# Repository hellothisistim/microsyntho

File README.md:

# microsyntho
Making synthesizers with microcontrollers

So, yeah... I'm learning about it. And it'll all get dumped here.

License: [CC-BY-SA](https://creativecommons.org/licenses/by-sa/4.0/)

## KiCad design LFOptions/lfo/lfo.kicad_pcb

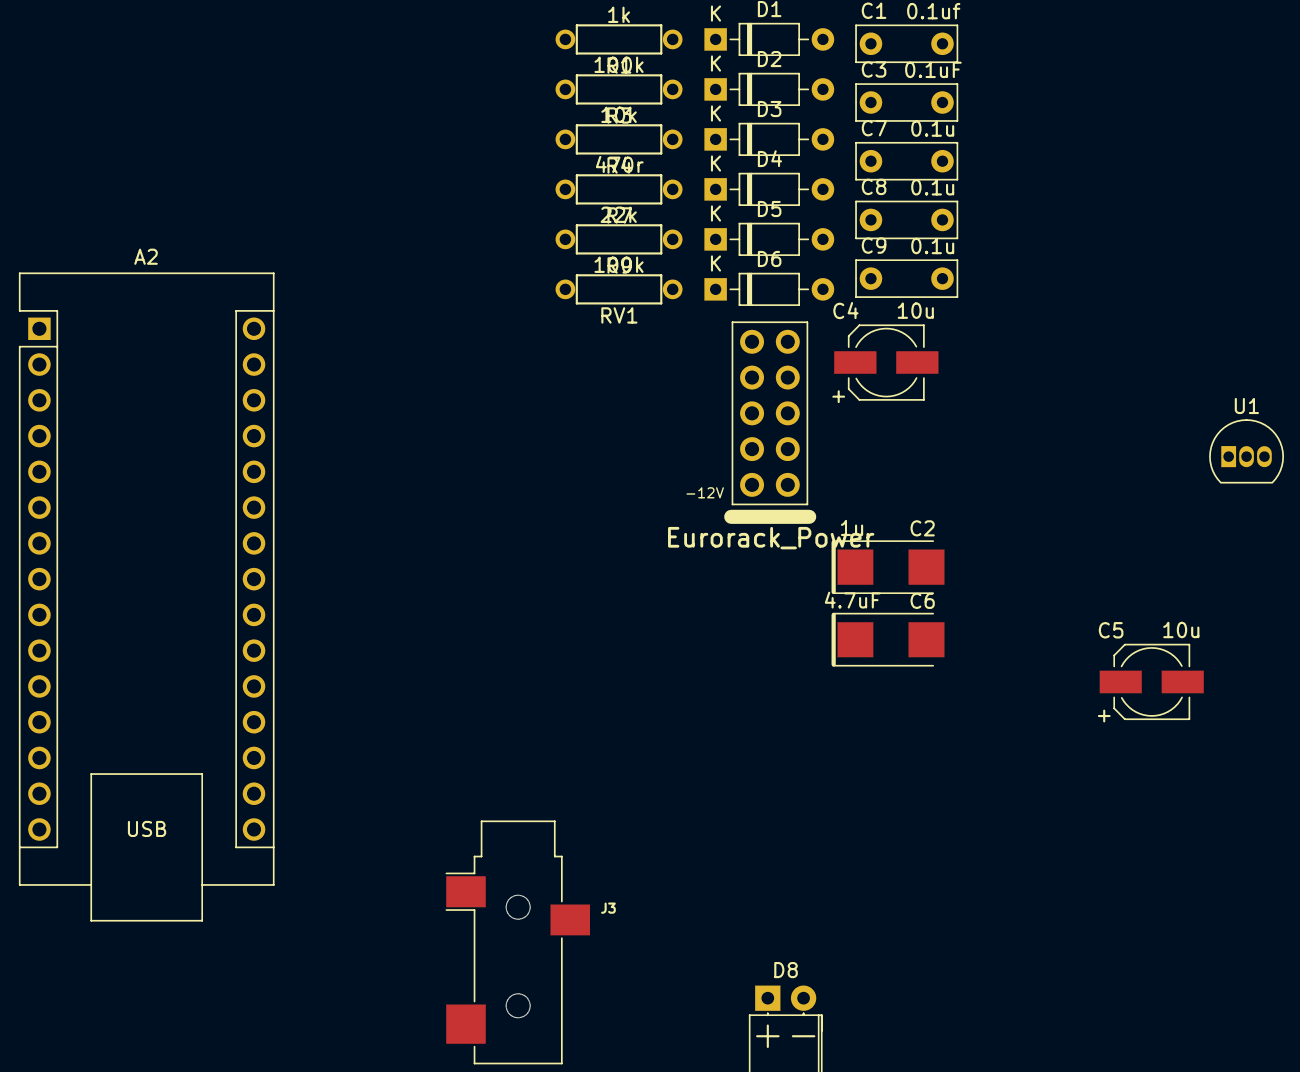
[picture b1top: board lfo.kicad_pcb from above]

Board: 2 copper layers, 26 parts (0 on the bottom side), 14 nets, no tracks yet.

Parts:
A2: Arduino_Nano_v3.x; Arduino_Nano
C1: 0.1uf; C_Disc_P5.08mm
C2: 1u; CP_Tantalum_EIA-6032-28_Kemet-C
C3: 0.1uF; C_Disc_P5.08mm
C4, C5: 10u; CP_Elec_5x5.3
C6: 4.7uF; CP_Tantalum_EIA-6032-28_Kemet-C
C7, C8, C9: 0.1u; C_Disc_P5.08mm
D1, D2, D3, D4, D5, D6: BAT43; D_DO-35_SOD27_P7.62mm_Horizontal
D8: LED_Small; LED_5mm_RightAngle
J2: Eurorack_Power; Pins_2x05_2.54mm_TH_Europower
J3: AudioJack2_SwitchT; Jack_3.5mm_CUI_SJ-3523-SMT_Horizontal
R1: 1k; R_Axial_DIN0207_L6.3mm_D2.5mm_P7.62mm_Horizontal
R3: 100k; R_Axial_DIN0207_L6.3mm_D2.5mm_P7.62mm_Horizontal
R4: 10k; R_Axial_DIN0207_L6.3mm_D2.5mm_P7.62mm_Horizontal
R7: 470r; R_Axial_DIN0207_L6.3mm_D2.5mm_P7.62mm_Horizontal
R9: 22k; R_Axial_DIN0207_L6.3mm_D2.5mm_P7.62mm_Horizontal
RV1: 100k; R_Axial_DIN0207_L6.3mm_D2.5mm_P7.62mm_Horizontal
U1: LM78L05_TO92; TO-92_Inline

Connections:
+5V: C9.1, D1.1 (K), D5.1 (K), RV1.1, U1.1 (VO)
+12V: A2.30 (VIN), C4.1, C7.1, D3.1 (K), U1.3 (VI)
CV: A2.6 (D3), A2.26 (A7), C3.1, D1.2 (A), D2.1 (K), R4.2
CVout: A2.10 (D7), D5.2 (A), D6.1 (K), R7.1, R9.1
GNDPWR: A2.4 (GND), A2.29 (GND), C1.2, C2.1, C3.2, C4.2, C5.1, C6.2, C7.2, C8.1, C9.2, D2.2 (A), D6.2 (A), D8.1 (K), J2.3 (GND), J2.4 (GND), J2.5 (GND), J2.6 (GND), J2.7 (GND), J2.8 (GND), J3.S, R3.2, U1.2 (GND)
unnamed: A2.18 (AREF), C2.2
unnamed: C6.1, J3.T, R7.2
unnamed: D3.2 (A), J2.9 (+12V), J2.10 (+12V)
unnamed: C5.2, C8.2, D4.2 (A)
unnamed: D4.1 (K), J2.1 (-12V), J2.2 (-12V)
unnamed: D8.2 (A), R9.2
unnamed: R3.1, R4.1
unnamed: R1.2, RV1.2
knob: A2.19 (A0), C1.1, R1.1

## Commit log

2024-11-04 Correct typo
2024-11-04 Progress. Currently broken.
2024-11-08 Add circuit diagram
2024-11-08 Ignore backups
